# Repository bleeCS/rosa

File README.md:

# rosa
 60% PCB Commission for Oggi

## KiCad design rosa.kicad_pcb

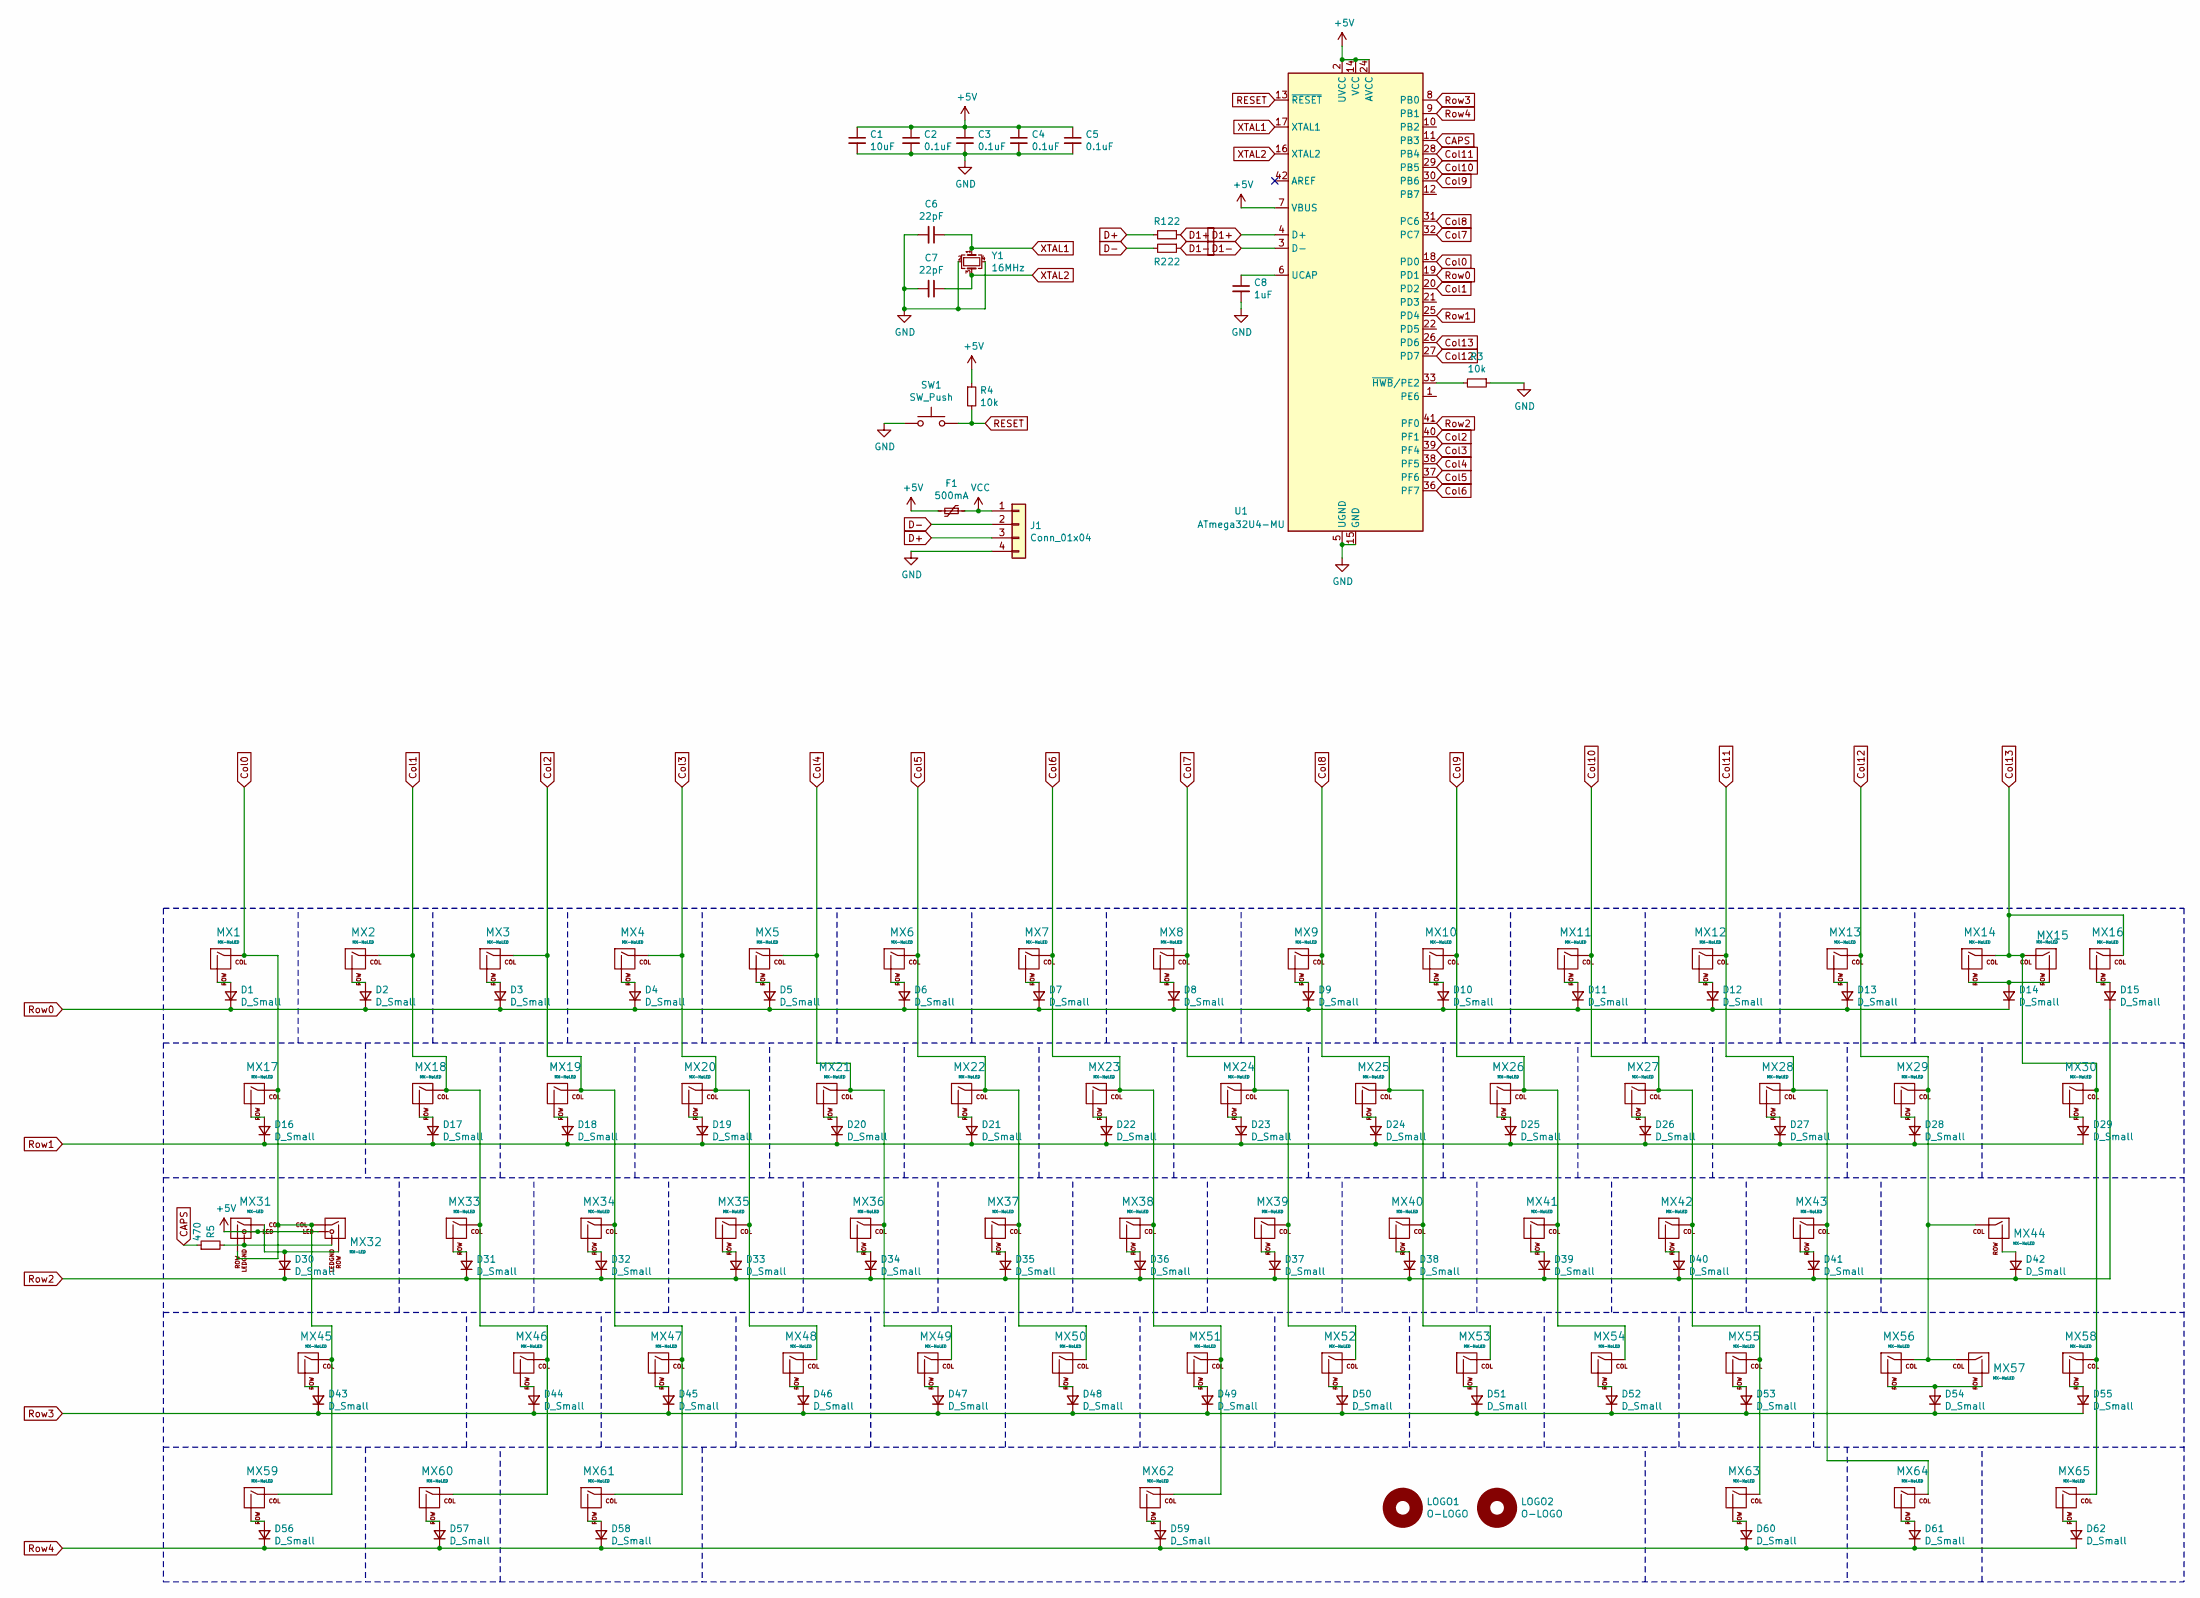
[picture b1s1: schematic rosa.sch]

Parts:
C1: 10uF; C_0603_1608Metric
C2, C3, C4, C5: 0.1uF; C_0603_1608Metric
C6, C7: 22pF; C_0603_1608Metric
C8: 1uF; C_0603_1608Metric
D1, D2, D3, D4, D5, D6, D7, D8, D9, D10, D11, D12, D13, D14, D15, D16, D17, D18, D19, D20, D21, D22, D23, D24, D25, D26, D27, D28, D29, D30, D31, D32, D33, D34, D35, D36, D37, D38, D39, D40, D41, D42, D43, D44, D45, D46, D47, D48, D49, D50, D51, D52, D53, D54, D55, D56, D57, D58, D59, D60, D61, D62: D_Small; D_SOD-123
F1: 500mA; Fuse_1206_3216Metric
J1: Conn_01x04; JST-SR-4
LOGO1: O-LOGO; MY-LOGO-SVG
LOGO2: O-LOGO; oggi-logo
MX1, MX2, MX3, MX4, MX5, MX6, MX7, MX8, MX9, MX10, MX11, MX12, MX13, MX15, MX16, MX18, MX19, MX20, MX21, MX22, MX23, MX24, MX25, MX26, MX27, MX28, MX29, MX33, MX34, MX35, MX36, MX37, MX38, MX39, MX40, MX41, MX42, MX43, MX46, MX47, MX48, MX49, MX50, MX51, MX52, MX53, MX54, MX55, MX58, MX60, MX64: MX-NoLED; MXOnly-1U-NoLED
MX14: MX-NoLED; MXOnly-2U-NoLED
MX17, MX30, MX59, MX61, MX63, MX65: MX-NoLED; MXOnly-1.5U-NoLED
MX31: MX-LED; MXOnly-1.25U-FLIPPED
MX32: MX-LED; MXOnly-1.75U
MX44: MX-NoLED; MXOnly-2.25U-ReversedStabilizers-NoLED
MX45: MX-NoLED; MXOnly-2.25U-NoLED
MX56: MX-NoLED; MXOnly-1.75U-NoLED
MX57: MX-NoLED; MXOnly-2.75U-NoLED
MX62: MX-NoLED; MXOnly-7U-ReversedStabilizers-NoLED
R1, R2: 22; R_0603_1608Metric
R3, R4: 10k; R_0603_1608Metric
R5: 470; R_0603_1608Metric
SW1: SW_Push; K2-1187SQ-A4SW-06
U1: ATmega32U4-MU; QFN-44-1EP_7x7mm_P0.5mm_EP5.2x5.2mm
Y1: 16MHz; Crystal_SMD_3225-4Pin_3.2x2.5mm

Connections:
+5V: C1.1, C2.1, C3.1, C4.1, C5.1, F1.2, MX31.3 (LED), MX32.3 (LED), R4.1, U1.2 (UVCC), U1.7 (VBUS), U1.14 (VCC), U1.24 (AVCC), U1.34 (VCC), U1.44 (AVCC)
CAPS: R5.1, U1.11 (PB3)
Col0: MX1.1 (COL), MX17.1 (COL), MX31.2 (ROW), MX32.1 (COL), MX45.1 (COL), MX59.1 (COL), U1.18 (PD0)
Col1: MX2.1 (COL), MX18.1 (COL), MX33.1 (COL), MX46.1 (COL), MX60.1 (COL), U1.20 (PD2)
Col2: MX3.1 (COL), MX19.1 (COL), MX34.1 (COL), MX47.1 (COL), MX61.1 (COL), U1.40 (PF1)
Col3: MX4.1 (COL), MX20.1 (COL), MX35.1 (COL), MX48.1 (COL), U1.39 (PF4)
Col4: MX5.1 (COL), MX21.1 (COL), MX36.1 (COL), MX49.1 (COL), U1.38 (PF5)
Col5: MX6.1 (COL), MX22.1 (COL), MX37.1 (COL), MX50.1 (COL), U1.37 (PF6)
Col6: MX7.1 (COL), MX23.1 (COL), MX38.1 (COL), MX51.1 (COL), MX62.1 (COL), U1.36 (PF7)
Col7: MX8.1 (COL), MX24.1 (COL), MX39.1 (COL), MX52.1 (COL), U1.32 (PC7)
Col8: MX9.1 (COL), MX25.1 (COL), MX40.1 (COL), MX53.1 (COL), U1.31 (PC6)
Col9: MX10.1 (COL), MX26.1 (COL), MX41.1 (COL), MX54.1 (COL), U1.30 (PB6)
Col10: MX11.1 (COL), MX27.1 (COL), MX42.1 (COL), MX55.1 (COL), MX63.1 (COL), U1.29 (PB5)
Col11: MX12.1 (COL), MX28.1 (COL), MX43.1 (COL), MX64.1 (COL), U1.28 (PB4)
Col12: MX13.1 (COL), MX29.1 (COL), MX44.1 (COL), MX56.1 (COL), MX57.1 (COL), U1.27 (PD7)
Col13: MX14.1 (COL), MX15.1 (COL), MX16.1 (COL), MX30.1 (COL), MX58.1 (COL), MX65.1 (COL), U1.26 (PD6)
D1+: R1.1, U1.4 (D+)
D1-: R2.1, U1.3 (D-)
D+: J1.3, R1.2
D-: J1.2, R2.2
GND: C1.2, C2.2, C3.2, C4.2, C5.2, C6.2, C7.2, C8.2, J1.4, R3.1, SW1.1, U1.5 (UGND), U1.15 (GND), U1.23 (GND), U1.35 (GND), U1.43 (GND), U1.45 (GND), Y1.2, Y1.4
unnamed: C8.1, U1.6 (UCAP)
unnamed: D1.2 (A), MX1.2 (ROW)
unnamed: D2.2 (A), MX2.2 (ROW)
unnamed: D3.2 (A), MX3.2 (ROW)
unnamed: D4.2 (A), MX4.2 (ROW)
unnamed: D5.2 (A), MX5.2 (ROW)
unnamed: D6.2 (A), MX6.2 (ROW)
unnamed: D7.2 (A), MX7.2 (ROW)
unnamed: D8.2 (A), MX8.2 (ROW)
unnamed: D9.2 (A), MX9.2 (ROW)
unnamed: D10.2 (A), MX10.2 (ROW)
unnamed: D11.2 (A), MX11.2 (ROW)
unnamed: D12.2 (A), MX12.2 (ROW)
unnamed: D13.2 (A), MX13.2 (ROW)
unnamed: D14.2 (A), MX14.2 (ROW), MX15.2 (ROW)
unnamed: D15.2 (A), MX16.2 (ROW)
unnamed: D16.2 (A), MX17.2 (ROW)
unnamed: D17.2 (A), MX18.2 (ROW)
unnamed: D18.2 (A), MX19.2 (ROW)
unnamed: D19.2 (A), MX20.2 (ROW)
unnamed: D20.2 (A), MX21.2 (ROW)
unnamed: D21.2 (A), MX22.2 (ROW)
unnamed: D22.2 (A), MX23.2 (ROW)
unnamed: D23.2 (A), MX24.2 (ROW)
unnamed: D24.2 (A), MX25.2 (ROW)
unnamed: D25.2 (A), MX26.2 (ROW)
unnamed: D26.2 (A), MX27.2 (ROW)
unnamed: D27.2 (A), MX28.2 (ROW)
unnamed: D28.2 (A), MX29.2 (ROW)
unnamed: D29.2 (A), MX30.2 (ROW)
unnamed: D30.2 (A), MX31.1 (COL), MX32.2 (ROW)
unnamed: D31.2 (A), MX33.2 (ROW)
unnamed: D32.2 (A), MX34.2 (ROW)
unnamed: D33.2 (A), MX35.2 (ROW)
unnamed: D34.2 (A), MX36.2 (ROW)
unnamed: D35.2 (A), MX37.2 (ROW)
unnamed: D36.2 (A), MX38.2 (ROW)
unnamed: D37.2 (A), MX39.2 (ROW)
unnamed: D38.2 (A), MX40.2 (ROW)
unnamed: D39.2 (A), MX41.2 (ROW)
unnamed: D40.2 (A), MX42.2 (ROW)
unnamed: D41.2 (A), MX43.2 (ROW)
unnamed: D42.2 (A), MX44.2 (ROW)
unnamed: D43.2 (A), MX45.2 (ROW)
unnamed: D44.2 (A), MX46.2 (ROW)
unnamed: D45.2 (A), MX47.2 (ROW)
unnamed: D46.2 (A), MX48.2 (ROW)
unnamed: D47.2 (A), MX49.2 (ROW)
unnamed: D48.2 (A), MX50.2 (ROW)
unnamed: D49.2 (A), MX51.2 (ROW)
unnamed: D50.2 (A), MX52.2 (ROW)
unnamed: D51.2 (A), MX53.2 (ROW)
unnamed: D52.2 (A), MX54.2 (ROW)
unnamed: D53.2 (A), MX55.2 (ROW)
unnamed: D54.2 (A), MX56.2 (ROW), MX57.2 (ROW)
unnamed: D55.2 (A), MX58.2 (ROW)
unnamed: D56.2 (A), MX59.2 (ROW)
unnamed: D57.2 (A), MX60.2 (ROW)
unnamed: D58.2 (A), MX61.2 (ROW)
unnamed: D59.2 (A), MX62.2 (ROW)
unnamed: D60.2 (A), MX63.2 (ROW)
unnamed: D61.2 (A), MX64.2 (ROW)
unnamed: D62.2 (A), MX65.2 (ROW)
unnamed: MX31.4 (LEDGND), MX32.4 (LEDGND), R5.2
unnamed: R3.2, U1.33 (~HWB~/PE2)
RESET: R4.2, SW1.2, U1.13 (~RESET)
Row0: D1.1 (K), D2.1 (K), D3.1 (K), D4.1 (K), D5.1 (K), D6.1 (K), D7.1 (K), D8.1 (K), D9.1 (K), D10.1 (K), D11.1 (K), D12.1 (K), D13.1 (K), D14.1 (K), U1.19 (PD1)
Row1: D16.1 (K), D17.1 (K), D18.1 (K), D19.1 (K), D20.1 (K), D21.1 (K), D22.1 (K), D23.1 (K), D24.1 (K), D25.1 (K), D26.1 (K), D27.1 (K), D28.1 (K), D29.1 (K), U1.25 (PD4)
Row2: D15.1 (K), D30.1 (K), D31.1 (K), D32.1 (K), D33.1 (K), D34.1 (K), D35.1 (K), D36.1 (K), D37.1 (K), D38.1 (K), D39.1 (K), D40.1 (K), D41.1 (K), D42.1 (K), U1.41 (PF0)
Row3: D43.1 (K), D44.1 (K), D45.1 (K), D46.1 (K), D47.1 (K), D48.1 (K), D49.1 (K), D50.1 (K), D51.1 (K), D52.1 (K), D53.1 (K), D54.1 (K), D55.1 (K), U1.8 (PB0)
Row4: D56.1 (K), D57.1 (K), D58.1 (K), D59.1 (K), D60.1 (K), D61.1 (K), D62.1 (K), U1.9 (PB1)
VCC: F1.1, J1.1
XTAL1: C6.1, U1.17 (XTAL1), Y1.1
XTAL2: C7.1, U1.16 (XTAL2), Y1.3

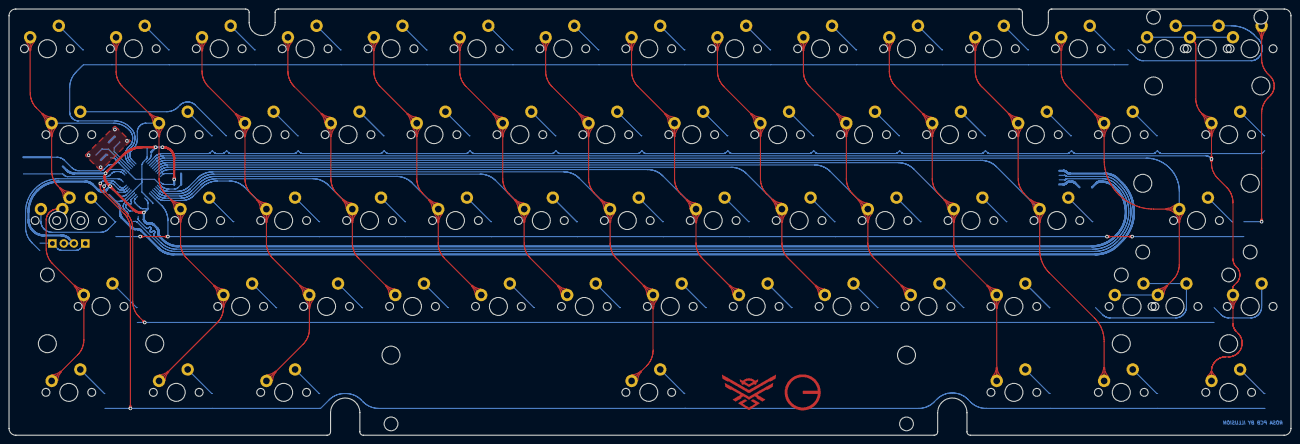
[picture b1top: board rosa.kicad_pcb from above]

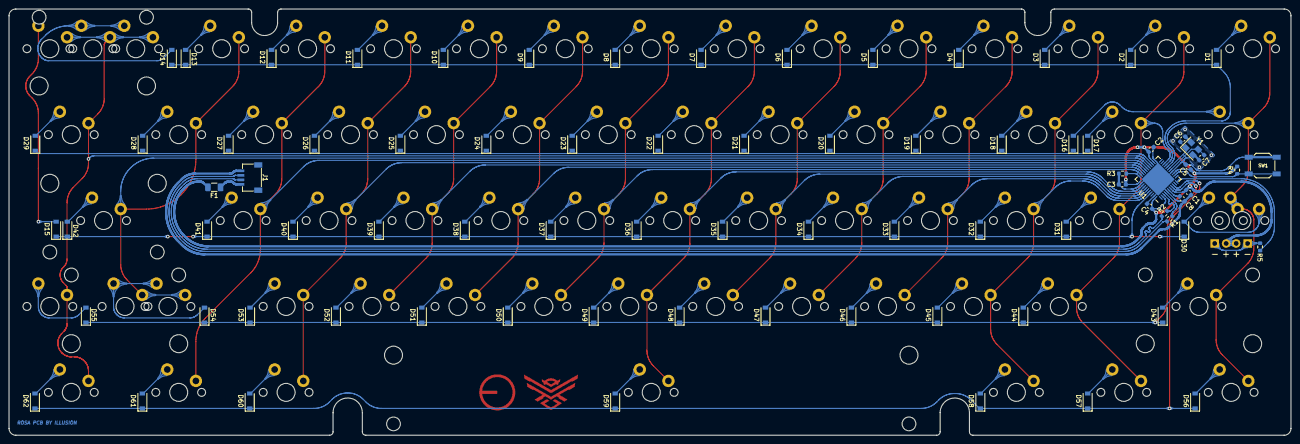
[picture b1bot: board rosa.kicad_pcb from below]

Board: 2 copper layers, 284.3 x 94.5 mm, 147 parts (80 on the bottom side), 95 nets.

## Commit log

2021-03-18 initialize project
2021-03-19 start schematic
2021-03-20 finish routing
2021-03-21 add pcb art
2021-03-22 routing tune up. finalize edge cuts, pcb art, and designator silkscreen. update git ignore.
2021-06-04 change caps lock indicator R value
2021-07-08 changes to fp-info-cache
